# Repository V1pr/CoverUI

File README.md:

# CoverUI for [OpenMower](https://github.com/ClemensElflein/OpenMower)

## About

This repository contains the firmware files required to use the mowers CoverUI (ButtonBoard).

## Variants

1. Custom DIY CoverUI-PCB which replaces the stock (top-cover) PCB.<br>
 Please check the [Cover UI board assembly instructions](<https://openmower.de/docs/cover-ui-assembly/>) for more detailed infos.<br>
 Also available in [Vermut's Shop](https://shop.devops.care/10-openmower) (as part of his 'Upgrade Kit')
1. Stock YardForce CoverUI for the following models:
   1. Classic 500 (STM32 & GD32 MCU)
   2. Classic 500B (STM32 & GD32 MCU)
   3. SA/SC/NX-Type (10 Buttons, 12 LEDs), PCB labeled with RM-ECOW-V1.0.0 (STM32 MCU)
   4. SA/SC/NX-Type (9 Buttons, 11 LEDs), PCB labeled with RM-ECOW-V1.1.0 (STM32 & GD32 MCU)
   5. NX100i (18 Buttons, 3 LEDs, 256*64 Pixel LC-Display), PCB labeled with RM-EC3-V1.1 (STM32 MCU)
   6. SAxPro (Rev6) 6 Buttons 240*128 Pixel LC-Display (STM32 MCU)
   
    For this, you need to solder some cables and flash a modified firmware to it.<br>
    Please check the detailed [Stock CoverUI Readme](Firmware/CoverUI/YardForce/README.md) (as you've also the option to use your stock 'hall', 'stop' and 'rain' cables).

+1. LegacyHAT, a HAT addon for non-uC original CoverUI (9 Buttons, 11 LEDs), HAT uses an STM32F4xx "black pill" (mind the pill size!) - UNTESTED (yet!)

## License

Distributed under the MIT License. See [LICENSE](LICENSE) for more information.

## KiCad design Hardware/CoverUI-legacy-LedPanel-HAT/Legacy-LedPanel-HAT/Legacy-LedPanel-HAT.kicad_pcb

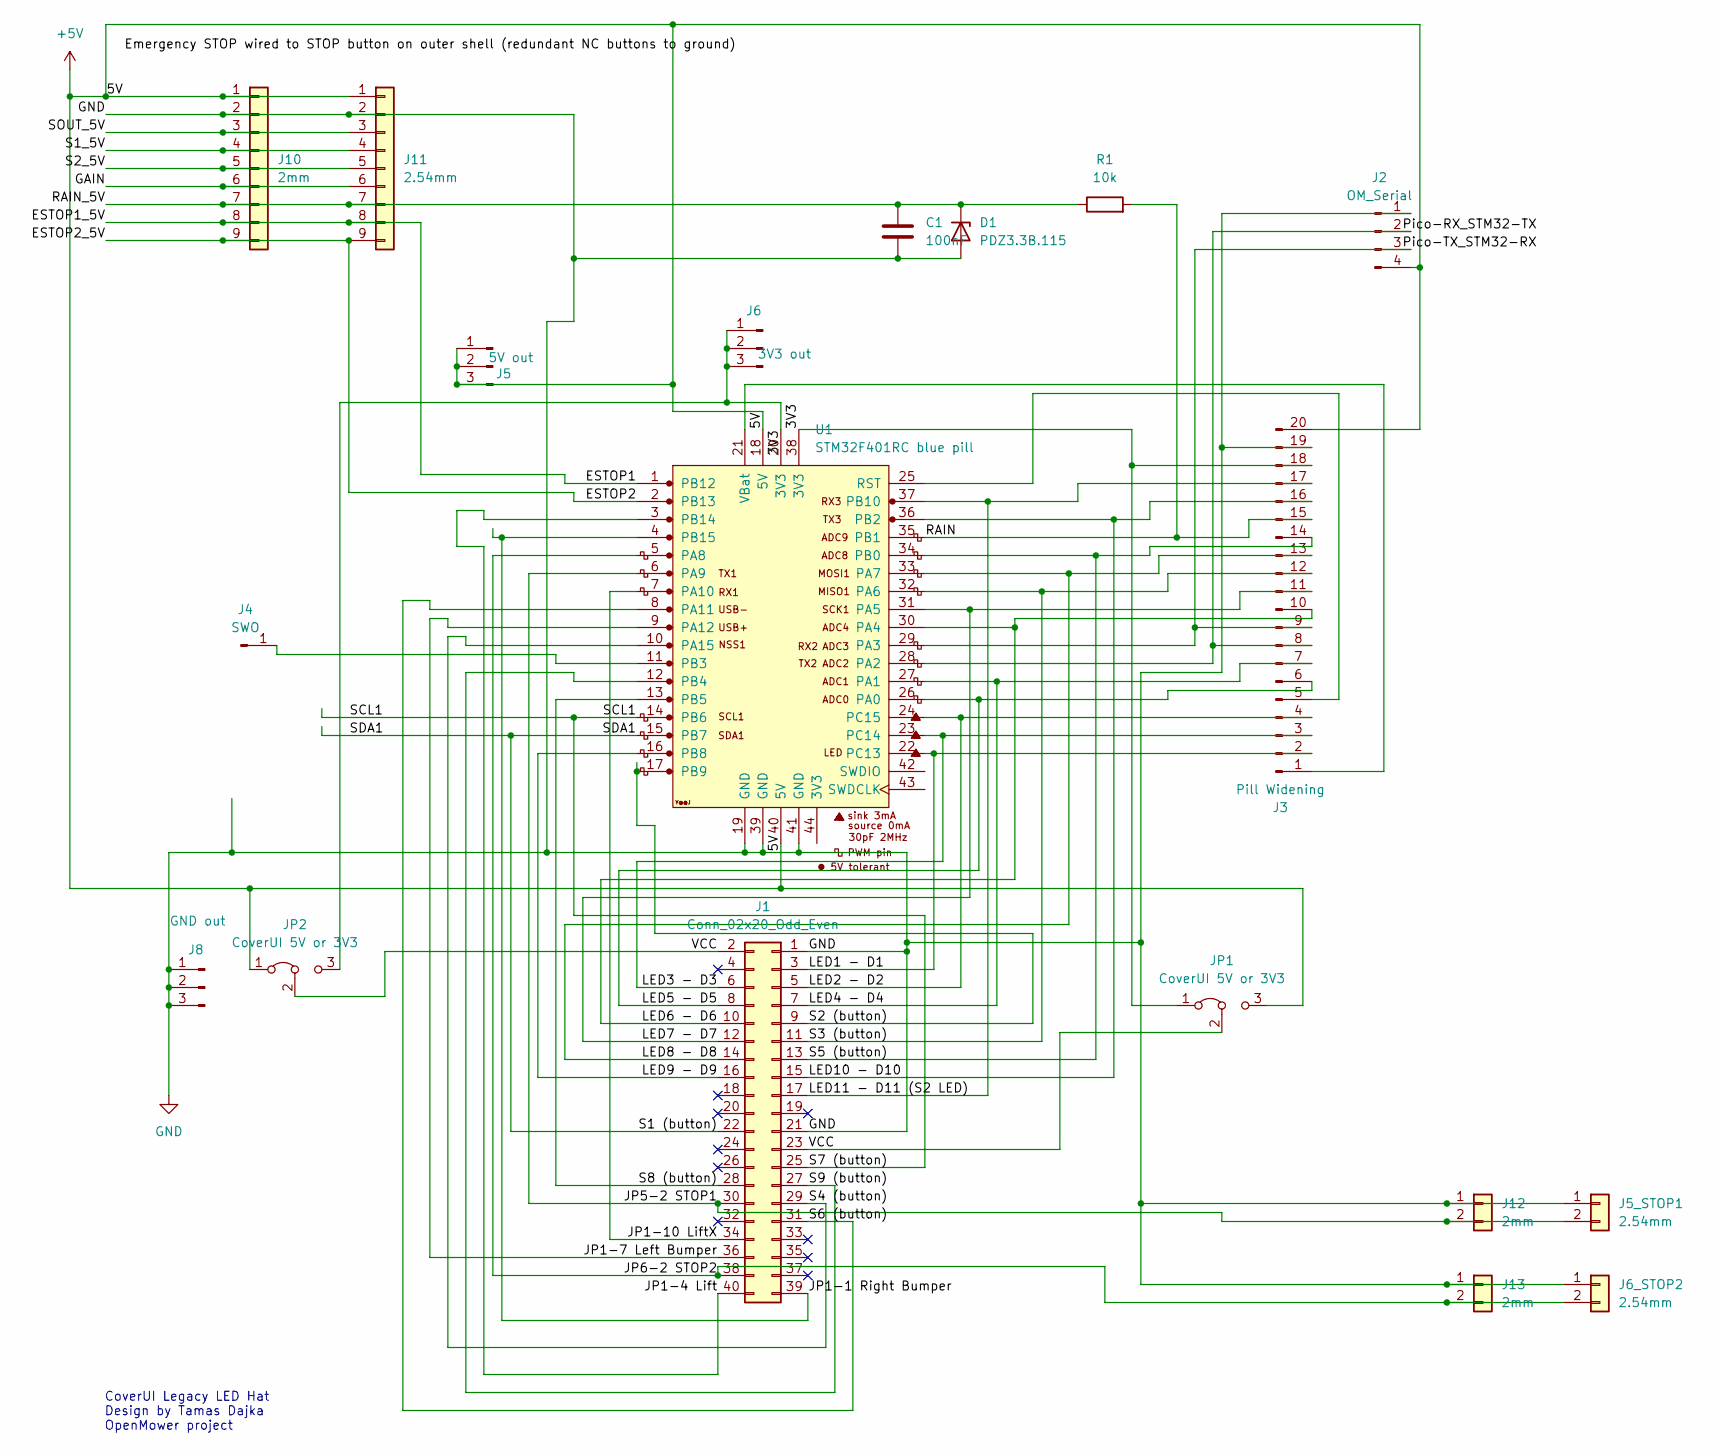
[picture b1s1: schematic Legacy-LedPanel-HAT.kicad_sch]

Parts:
C1: 100nF; C_1812_4532Metric
D1: PDZ3.3B.115; D_1812_4532Metric
J1: Conn_02x20_Odd_Even; PinHeader_2x20_P2.54mm_Vertical
J2: OM_Serial; JST_XH_S4B-XH-A_1x04_P2.50mm_Horizontal
J3: Pill Widening; PinHeader_1x20_P2.54mm_Vertical
J4: SWO; PinHeader_1x01_P2.54mm_Vertical
J5: 5V out; PinHeader_1x03_P2.54mm_Vertical
J5_STOP1, J6_STOP2: 2.54mm; JST_XH_B2B-XH-A_1x02_P2.50mm_Vertical
J6: 3V3 out; PinHeader_1x03_P2.54mm_Vertical
J8: GND out; PinHeader_1x03_P2.54mm_Vertical
J10: 2mm; JST_PH_B9B-PH-K_1x09_P2.00mm_Vertical
J11: 2.54mm; JST_XH_B9B-XH-A_1x09_P2.50mm_Vertical
J12, J13: 2mm; JST_PH_B2B-PH-K_1x02_P2.00mm_Vertical
JP1, JP2: CoverUI 5V or 3V3; PinHeader_1x03_P2.54mm_Vertical
R1: 10k; R_1812_4532Metric_Pad1.30x3.40mm_HandSolder
U1: STM32F401RC blue pill; YAAJ_WeAct_BlackPill_SWD_2

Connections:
+5V: J2.4, J3.20, J5.1, J5.2, J5.3, J10.1, J11.1, JP1.3 (B), JP2.1 (A), U1.18 (5V), U1.40 (5V)
/3V3: J3.18, J6.1, J6.2, J6.3, JP1.1 (A), JP2.3 (B), U1.20 (3V3), U1.38 (3V3)
/ESTOP1: J10.8, J11.8, U1.1 (PB12)
/ESTOP2: J10.9, J11.9, U1.2 (PB13)
/GAIN: J10.6, J11.6
/JP1-1 Right Bumper: J1.39, U1.4 (PB15)
/JP1-4 Lift: J1.40, U1.3 (PB14)
/JP1-7 Left Bumper: J1.36, U1.9 (PA12)
/JP1-10 LiftX: J1.34, U1.7 (PA10)
/JP5-2 STOP1: J1.30, J5_STOP1.2, J12.2, U1.6 (PA9)
/JP6-2 STOP2: J1.38, J6_STOP2.2, J13.2, U1.5 (PA8)
/LED1 - D1: J1.3, J3.2, U1.22 (PC13)
/LED2 - D2: J1.5, J3.4, U1.24 (PC15)
/LED3 - D3: J1.6, J3.3, U1.23 (PC14)
/LED4 - D4: J1.7, J3.7, U1.27 (PA1)
/LED5 - D5: J1.8, J3.6, U1.26 (PA0)
/LED6 - D6: J1.10, J3.10, U1.30 (PA4)
/LED7 - D7: J1.12, J3.11, U1.31 (PA5)
/LED8 - D8: J1.14, J3.13, U1.33 (PA7)
/LED9 - D9: J1.16, U1.16 (PB8)
/LED10 - D10: J1.15, J3.16, U1.36 (PB2)
/LED11 - D11 (S2 LED): J1.17, J3.17, U1.37 (PB10)
/Pico-RX_STM32-TX: J2.2, J3.8, U1.28 (PA2)
/Pico-TX_STM32-RX: J2.3, J3.9, U1.29 (PA3)
/RAIN: J3.15, R1.2, U1.35 (PB1)
/RAIN_5V: C1.1, D1.1 (K), J10.7, J11.7, R1.1
/S1 (button): J1.22, U1.15 (PB7)
/S1_5V: J10.4, J11.4
/S2 (button): J1.9, U1.17 (PB9)
/S2_5V: J10.5, J11.5
/S3 (button): J1.11, J3.12, U1.32 (PA6)
/S4 (button): J1.29, U1.10 (PA15)
/S5 (button): J1.13, J3.14, U1.34 (PB0)
/S6 (button): J1.31, U1.8 (PA11)
/S7 (button): J1.25, U1.14 (PB6)
/S8 (button): J1.28, U1.13 (PB5)
/S9 (button): J1.27, U1.12 (PB4)
/SOUT_5V: J10.3, J11.3
/VCC: J1.2, J1.23, JP1.2 (C), JP2.2 (C)
GND: C1.2, D1.2 (A), J1.1, J1.21, J2.1, J3.19, J5_STOP1.1, J6_STOP2.1, J8.1, J8.2, J8.3, J10.2, J11.2, J12.1, J13.1, U1.19 (GND), U1.39 (GND), U1.41 (GND)
unnamed: J3.1, U1.21 (VBat)
unnamed: J3.5, U1.25 (RST)
unnamed: J4.1, U1.11 (PB3)

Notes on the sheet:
CoverUI Legacy LED Hat Design by Tamas Dajka OpenMower project

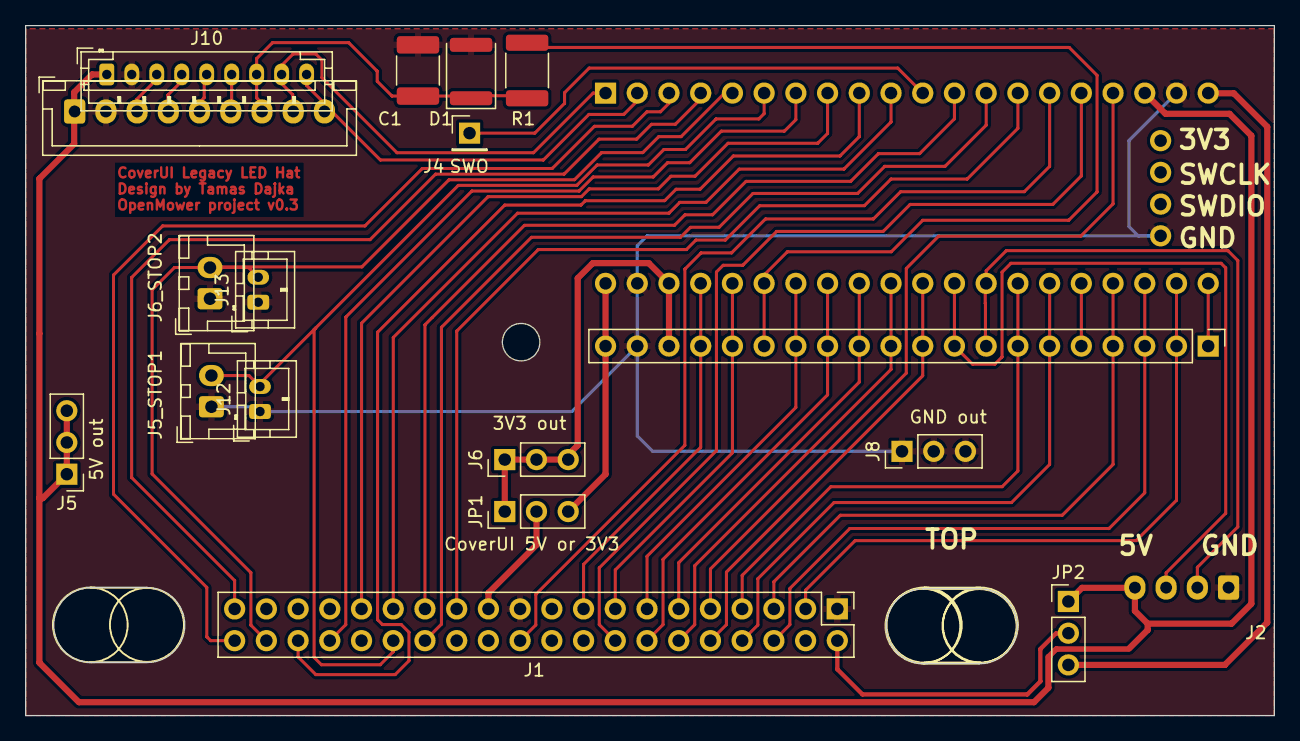
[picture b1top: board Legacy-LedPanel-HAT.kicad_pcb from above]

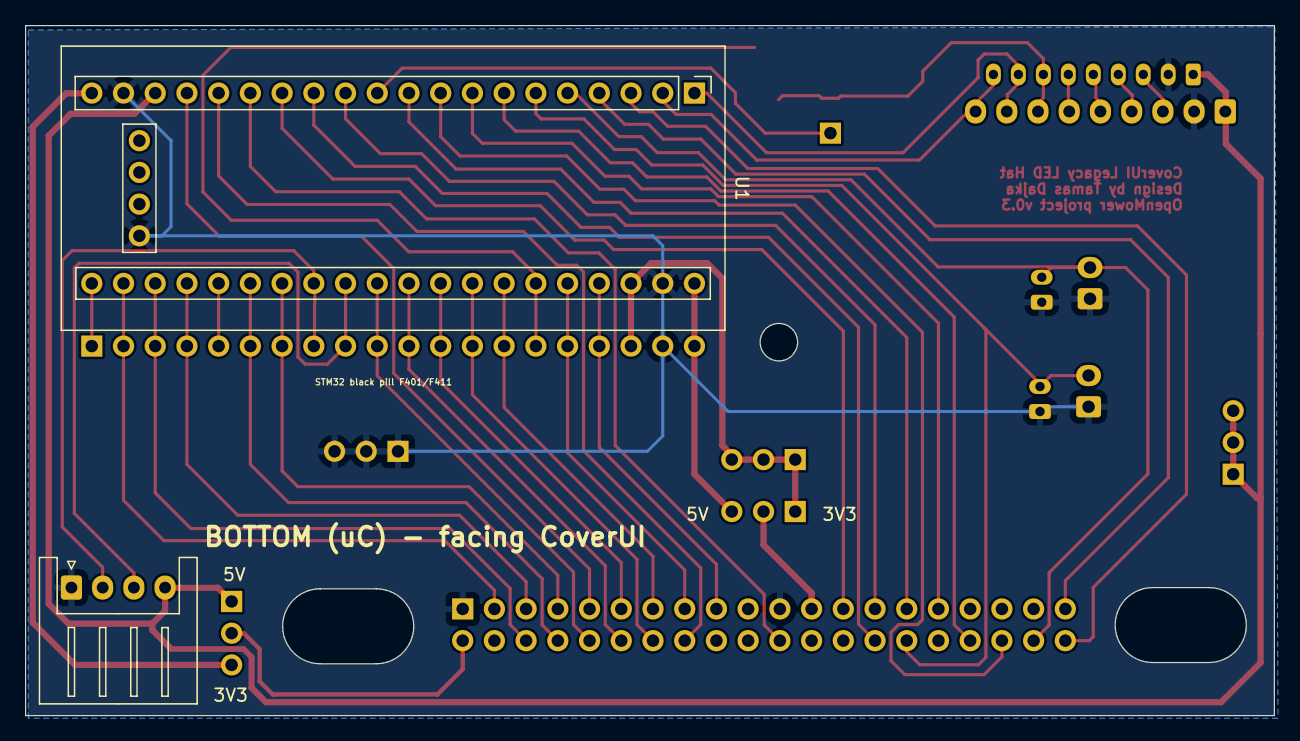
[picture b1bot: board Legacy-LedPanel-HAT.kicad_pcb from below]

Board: 2 copper layers, 100.0 x 55.3 mm, 19 parts (2 on the bottom side), 43 nets.

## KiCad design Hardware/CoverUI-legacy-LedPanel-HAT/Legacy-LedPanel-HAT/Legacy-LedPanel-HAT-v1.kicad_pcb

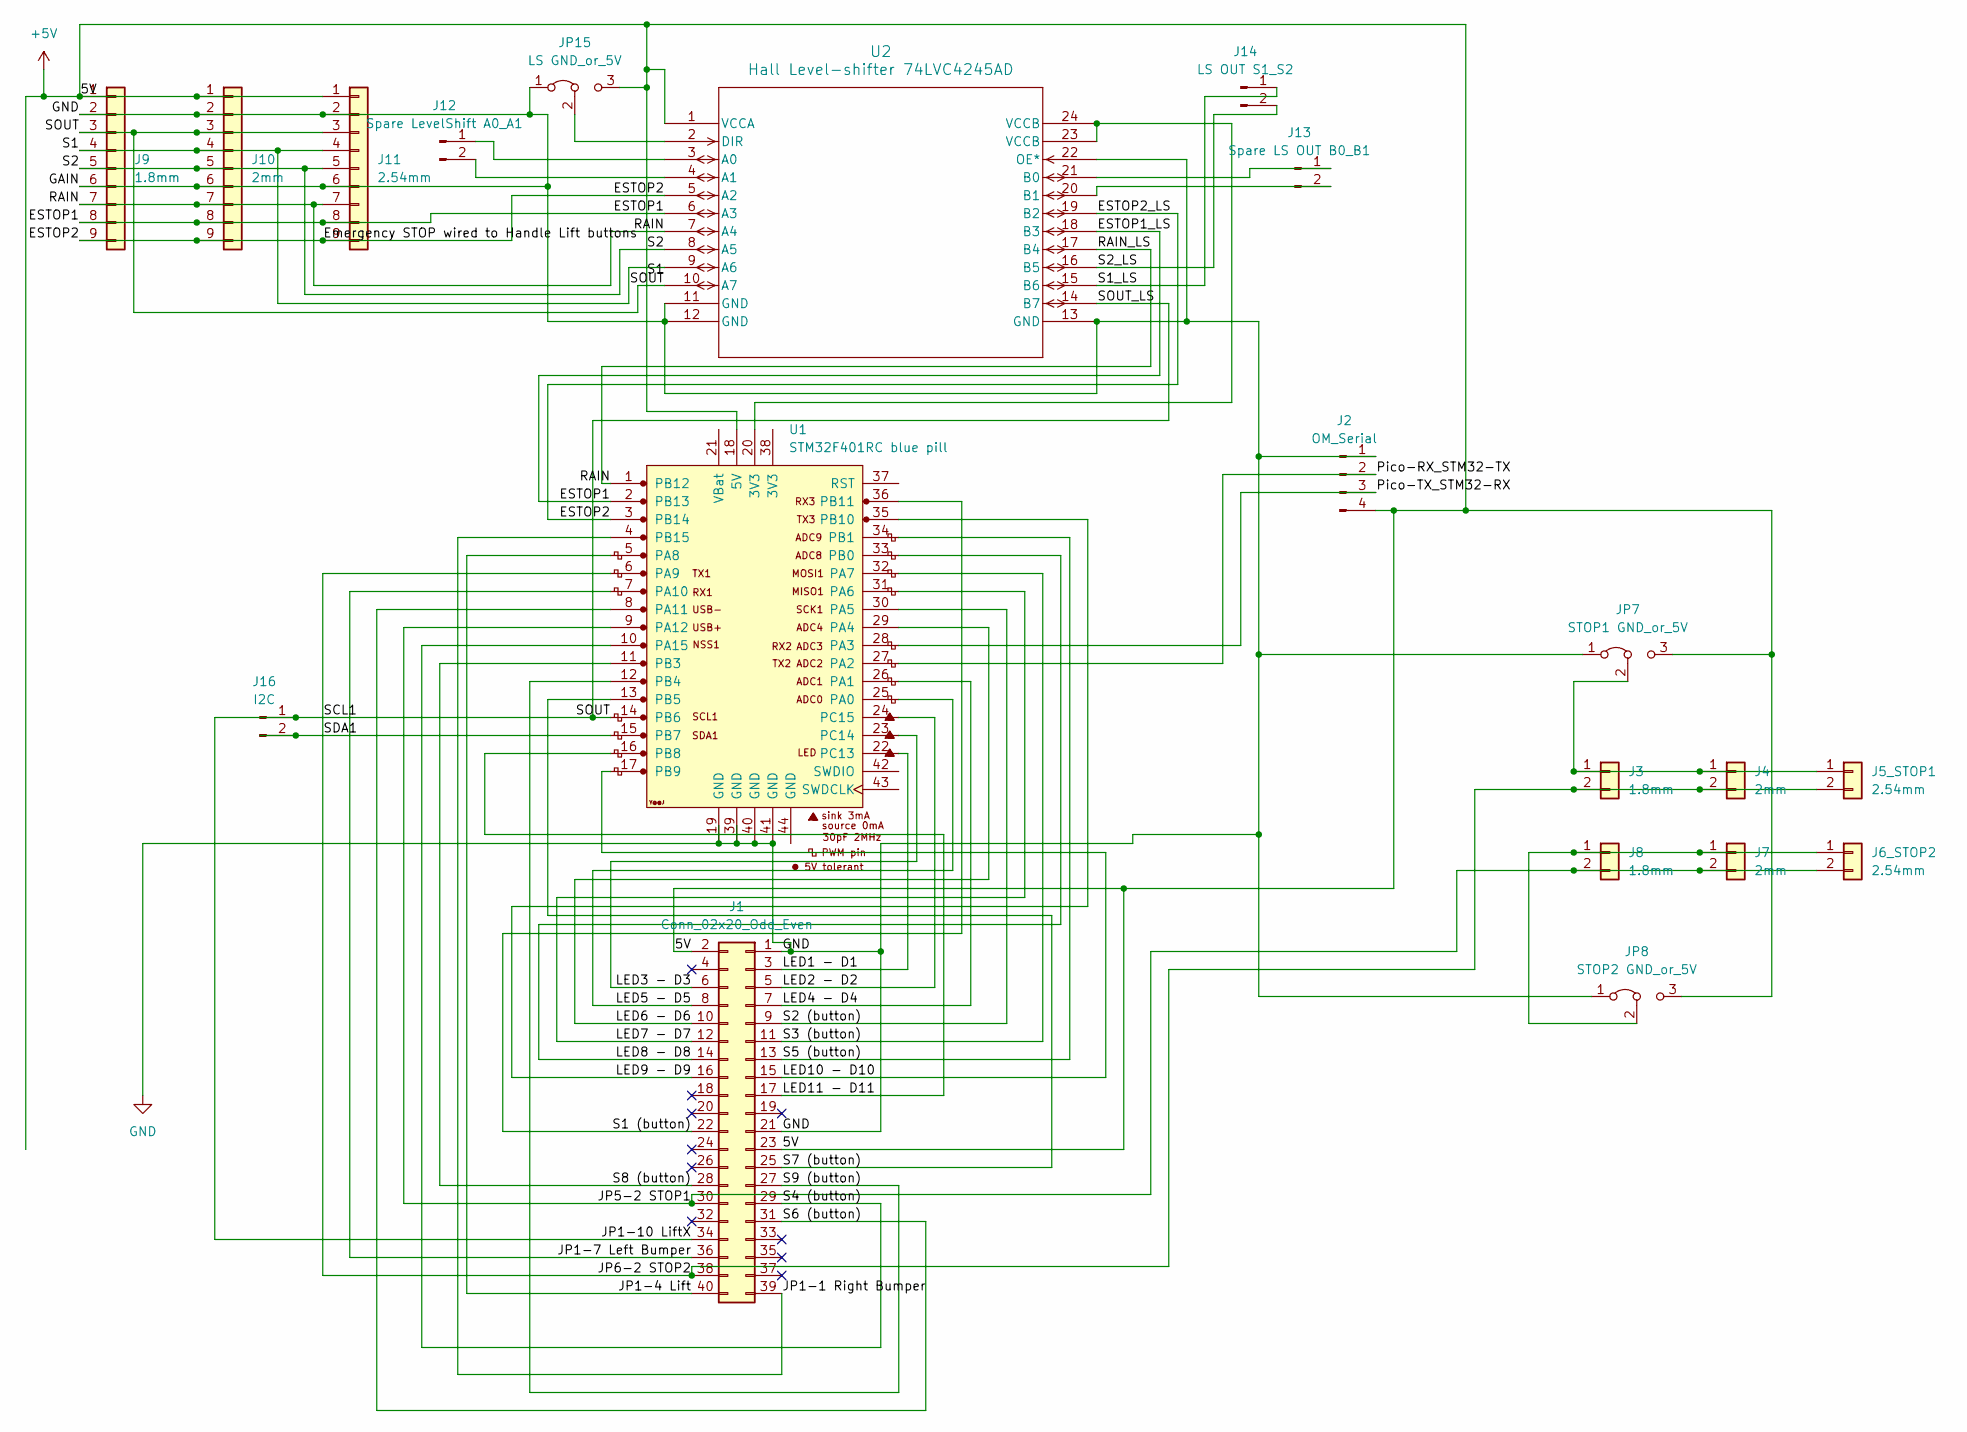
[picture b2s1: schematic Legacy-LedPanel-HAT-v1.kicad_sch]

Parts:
J1: Conn_02x20_Odd_Even; PinHeader_2x20_P2.54mm_Vertical
J2: OM_Serial; JST_XH_S4B-XH-A_1x04_P2.50mm_Horizontal
J3, J8: 1.8mm; conn_01x2_1.8mm
J4, J7: 2mm; JST_PH_B2B-PH-K_1x02_P2.00mm_Vertical
J5_STOP1, J6_STOP2: 2.54mm; JST_XH_B2B-XH-A_1x02_P2.50mm_Vertical
J9: 1.8mm; conn_01x9_1.8mm
J10: 2mm; JST_PH_S9B-PH-K_1x09_P2.00mm_Horizontal
J11: 2.54mm; JST_XH_S9B-XH-A-1_1x09_P2.50mm_Horizontal
J12: Spare LevelShift A0_A1; PinHeader_1x02_P2.54mm_Horizontal
J13: Spare LS OUT B0_B1; PinHeader_1x02_P2.54mm_Horizontal
J14: LS OUT S1_S2; PinHeader_1x02_P2.54mm_Horizontal
J16: I2C; PinHeader_1x02_P2.54mm_Horizontal
JP7: STOP1 GND_or_5V; PinHeader_1x03_P2.54mm_Vertical
JP8: STOP2 GND_or_5V; PinHeader_1x03_P2.54mm_Vertical
JP15: LS GND_or_5V; PinHeader_1x03_P2.54mm_Vertical
U1: STM32F401RC blue pill; YAAJ_BluePill_SWD_1
U2: Hall Level-shifter 74LVC4245AD; SOT137-1_NEX

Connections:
+5V: J1.2, J1.23, J2.4, J9.1, J10.1, J11.1, JP7.3 (B), JP8.3 (B), JP15.3 (B), U1.18 (5V), U2.1 (VCCA)
/ESTOP1: J9.8, J10.8, J11.8, U1.2 (PB13), U2.6 (A3), U2.18 (B3)
/ESTOP2: J9.9, J10.9, J11.9, U1.3 (PB14), U2.5 (A2), U2.19 (B2)
/JP1-1 Right Bumper: J1.39, U1.4 (PB15)
/JP1-4 Lift: J1.40, U1.5 (PA8)
/JP1-7 Left Bumper: J1.36, U1.7 (PA10)
/JP5-2 STOP1: J1.30, J6_STOP2.2, J7.2, J8.2, U1.9 (PA12)
/LED1 - D1: J1.3, U1.22 (PC13)
/LED2 - D2: J1.5, U1.24 (PC15)
/LED3 - D3: J1.6, U1.23 (PC14)
/LED4 - D4: J1.7, U1.26 (PA1)
/LED5 - D5: J1.8, U1.25 (PA0)
/LED6 - D6: J1.10, U1.29 (PA4)
/LED7 - D7: J1.12, U1.31 (PA6)
/LED8 - D8: J1.14, U1.33 (PB0)
/LED9 - D9: J1.16, U1.35 (PB10)
/LED10 - D10: J1.15, U1.17 (PB9)
/LED11 - D11: J1.17, U1.16 (PB8)
/Pico-RX_STM32-TX: J2.2, U1.27 (PA2)
/Pico-TX_STM32-RX: J2.3, U1.28 (PA3)
/RAIN: J9.7, J10.7, J11.7, U1.1 (PB12), U2.7 (A4), U2.17 (B4)
/S1: J9.4, J10.4, J11.4, U2.9 (A6)
/S1 (button): J1.22, U1.36 (PB11)
/S1_LS: J14.1, U2.15 (B6)
/S2: J9.5, J10.5, J11.5, U2.8 (A5)
/S2 (button): J1.9, U1.30 (PA5)
/S2_LS: J14.2, U2.16 (B5)
/S3 (button): J1.11, U1.32 (PA7)
/S4 (button): J1.29, U1.10 (PA15)
/S5 (button): J1.13, U1.34 (PB1)
/S6 (button): J1.31, U1.8 (PA11)
/S7 (button): J1.25, U1.13 (PB5)
/S8 (button): J1.28, U1.11 (PB3)
/S9 (button): J1.27, U1.12 (PB4)
GND: J1.1, J1.21, J2.1, J9.2, J9.6, J10.2, J10.6, J11.2, J11.6, JP7.1 (A), JP8.1 (A), JP15.1 (A), U1.19 (GND), U1.39 (GND), U1.40 (GND), U1.41 (GND), U2.11 (GND), U2.12 (GND), U2.13 (GND), U2.22 (OE*)
unnamed: J3.1, J4.1, J5_STOP1.1, JP7.2 (C)
unnamed: J6_STOP2.1, J7.1, J8.1, JP8.2 (C)
unnamed: J12.1, U2.3 (A0)
unnamed: J12.2, U2.4 (A1)
unnamed: J13.1, U2.21 (B0)
unnamed: J13.2, U2.20 (B1)
unnamed: JP15.2 (C), U2.2 (DIR)
unnamed: U1.20 (3V3), U2.23 (VCCB), U2.24 (VCCB)

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
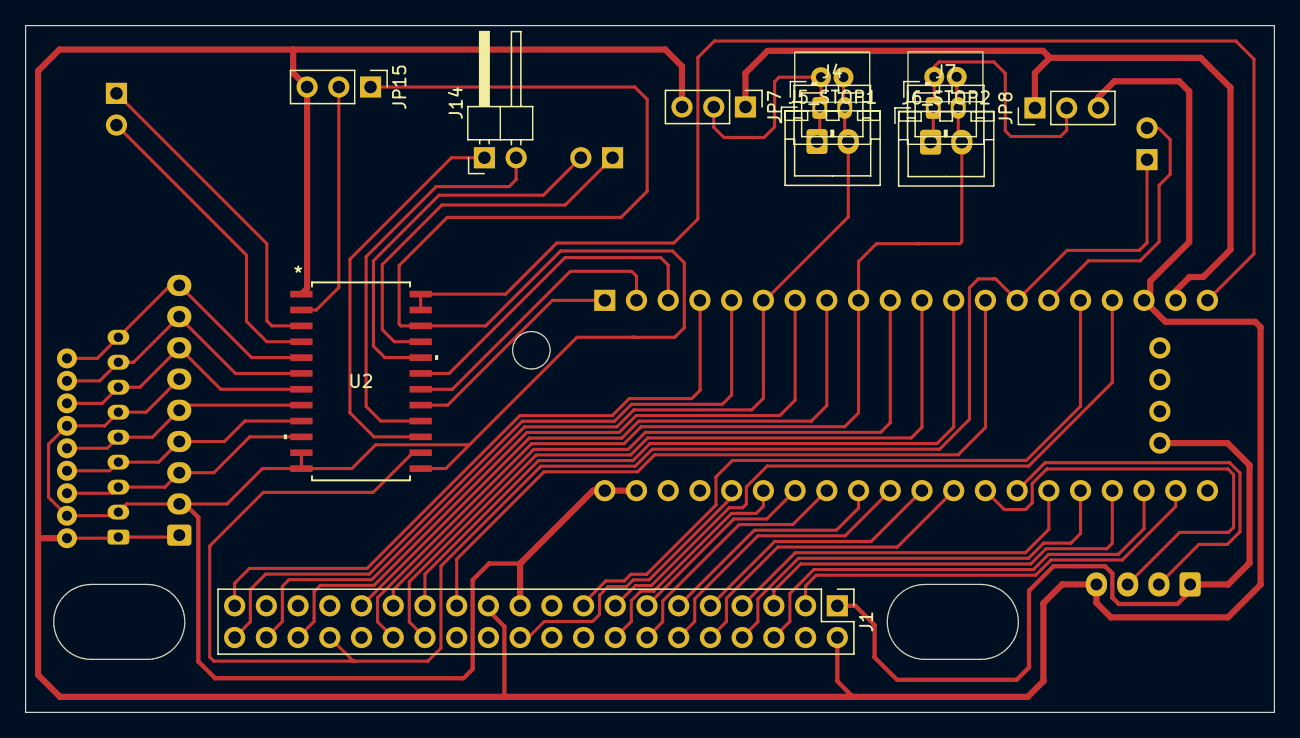
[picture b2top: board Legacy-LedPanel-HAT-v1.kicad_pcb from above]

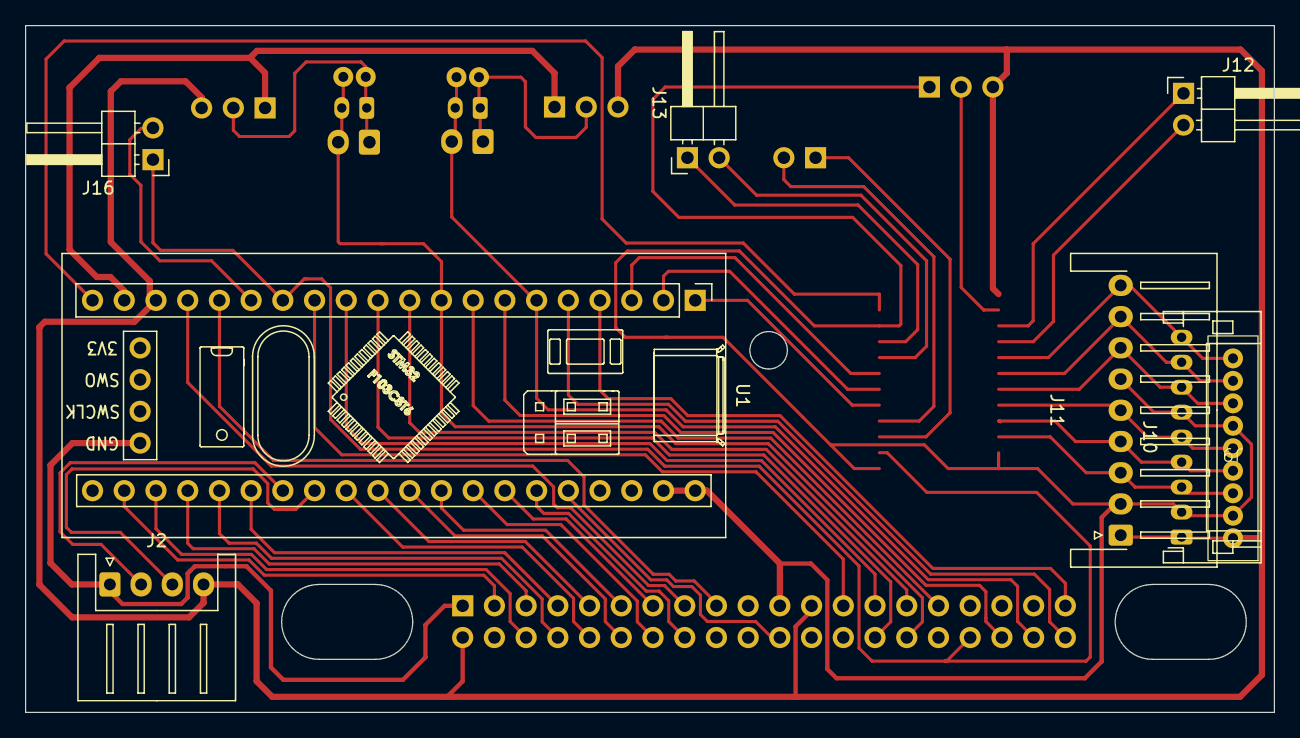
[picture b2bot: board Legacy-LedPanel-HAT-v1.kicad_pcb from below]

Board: 2 copper layers, 100.0 x 55.0 mm, 20 parts (8 on the bottom side), 46 nets.

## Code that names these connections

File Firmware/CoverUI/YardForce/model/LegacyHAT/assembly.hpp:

/**
 * @file model_LEGACYHAT.h
 * @author V1pr <viper @ vipernet (dot) hu>
 * @brief YardForce SA600ECO with non-uC UI panel + HAT module model header for OpenMower https://github.com/ClemensElflein/OpenMower
 * @version 0.1
 * @date 2025-04-15
 *
 * @copyright Copyright (c) 2023, 2024, 2025
 *
 */
#ifndef YARDFORCE_MDL_LEGACYHAT_ASSEMBLY_HPP
#define YARDFORCE_MDL_LEGACYHAT_ASSEMBLY_HPP

#include "../../include/Buttons.hpp"
#include "../../include/main.h"
#include "LEDcontrol.hpp"

#ifdef MOD_EMERGENCY
#include "../../include/Emergency.hpp"
#endif

/*
*
* PA11/PA12 is needed for USB CDC debug to work! Don't use it while debugging!
*
*/

// 1st row: Lifted, Wire (WLAN), Battery empty, Charge
#define LED_PIN_LIFTED PC13
#define LED_PIN_WIRE PC15
#define LED_PIN_BAT PC14
#define LED_PIN_CHARGE PA1

// 2nd row: 4,6,8,10HR
#define LED_PIN_4HR PA4
#define LED_PIN_6HR PA5
#define LED_PIN_8HR PA7
#define LED_PIN_10HR PA0

// 3rd row: S1, S2 + LOCK
#define LED_PIN_S1 PB8
#define LED_PIN_S2 PB10
#define LED_PIN_LOCK PB2 

/*
SW1 - play
SW2 - 10H
SW3 - 4h
SW4 - Home
SW5 - 6H
SW6 - 8H
SW7 - lock
SW8 - S1
SW9 - S2
*/

#define BTN_S1_PIN PB5 // SW8 - D10; PA15
#define BTN_S2_PIN PB4 // SW9 - D11; PB3
#define BTN_PLAY_PIN PB7 // SW1; PB5
#define BTN_HOME_PIN PA15 // SW4;
#define BTN_LOCK_PIN PB6 // SW7 - D9; PB4

#define BTN_4H_PIN PA6 // SW3 - 4H
#define BTN_6H_PIN PB0 // SW5 - 6H
#define BTN_8H_PIN PA11 // SW6 - 8H
#define BTN_10H_PIN PB9 // SW2 - 10H

// STOP button on the outer cover
#define PIN_ESTOP1 PB12 // ESTOP1 from original CoverUI - JP10 on LegacyHAT - 9 pin connector + LevelShift
#define PIN_ESTOP2 PB13 // ESTOP2 from original CoverUI - JP10 on LegacyHAT - 9 pin connector + LevelShift

// handle with 2 switches on either sidesx
#define PIN_HANDLE_BTN_1 PA9 // Handle Button1 - on the LegacyHAT, PB15 if on OEM-CoverUI
#ifndef USBD_USE_CDC // usb CDC debug uses PA11
#define PIN_HANDLE_BTN_2 PA8 // Handle Button2 - on the LegacyHAT, always routed to PA11
#endif

#define PIN_HALL1 PA10 // LiftX - JP1 pin 10 on OEM CoverUI
#ifdef USBD_USE_CDC
#define PIN_HALL2 PB15 // Left bumper - JP1 pin 7 on OEM CoverUI // we fake it to other pin, since PA12 is used by CDC
#else
#define PIN_HALL2 PA12 // Left bumper - JP1 pin 7 on OEM CoverUI
#endif

#define PIN_HALL3 PB14 // Lift - JP1 pin 4 on OEM CoverUI
#define PIN_HALL4 PB15 // Right bumper - JP1 pin 1 on OEM CoverUI

// checkme
#define PIN_RAIN PA1             
#define RAIN_ADC_THRESHOLD 700   // Why a threshold? Cause it could be made configurable on (Stock-)CoverUI (if i.e. required due to inaccuracy)
#define RAIN_PROCESS_PERIOD 5000 // c.ez proposed "once a second or every 10 seconds"

extern LEDcontrolLegacyHAT leds;

class ButtonsLegacyHAT : public Buttons {
    public:
     ButtonsLegacyHAT(const std::map<uint8_t, ButtonDef> &t_kBtnDefByNumMap) : Buttons(t_kBtnDefByNumMap) {};
 
     /**
      * @brief Check if one of the "magic buttons" got pressed and do his function.
      * LOCK + 4H = Display FW version
      * LOCK + 10H = LED animation
      */
     void handle_sys_req() override {
         if (!is_pressed(BTN_LOCK_NUM))
             return;
 
         if (is_pressed(BTN_10H_NUM))
             leds.sequence_start(&LEDcontrol::sequence_animate_handler);
         else if (is_pressed(BTN_4H_NUM))
             leds.show_num(FIRMWARE_VERSION);
         return;
     };
};
 
extern ButtonsLegacyHAT buttons;

// leds and buttons are needed!
#include "Hatch.hpp"

#ifdef MOD_RAIN
#include "../../include/Rain.hpp"
#endif

// LowLevel Serial Pins
#define UART_LL_RX PA3
#define UART_LL_TX PA2

#endif // YARDFORCE_MDL_LEGACYHAT_ASSEMBLY_HPP

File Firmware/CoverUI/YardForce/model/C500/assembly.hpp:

/**
 * @file C500/assembly.hpp
 * @author Apehaenger (joerg@ebeling.ws)
 * @brief YardForce Classic500 CoverUI Assembly for OpenMower https://github.com/ClemensElflein/OpenMower
 * @version 0.1
 * @date 2024-10-02
 *
 * @copyright Copyright (c) 2024
 *
 */
#ifndef YARDFORCE_MDL_C500_ASSEMBLY_HPP
#define YARDFORCE_MDL_C500_ASSEMBLY_HPP

#include "../../include/Buttons.hpp"
#include "../../include/main.h"
#include "LEDcontrol.hpp"

#ifdef MOD_EMERGENCY
#include "../../include/Emergency.hpp"
#endif

// ***** LEDs *****
// 1st row: 2,4,6,8HR
#define LED_PIN_2HR PA4
#define LED_PIN_4HR PA5
#define LED_PIN_6HR PA6
#define LED_PIN_8HR PA7
// 2nd row: S1, S2, LOCK
#define LED_PIN_S1 PA0
#define LED_PIN_S2 PA1
#define LED_PIN_LOCK PC4
// 3rd row: Mon-Sun
#define LED_PIN_MON PA15
#define LED_PIN_TUE PC10
#define LED_PIN_WED PC11
#define LED_PIN_THU PC12
#define LED_PIN_FRI PD2
#define LED_PIN_SAT PB3
#define LED_PIN_SUN PB4
// 4th row: Lifted, Wire, Bat, Charge
#define LED_PIN_LIFTED PC0
#define LED_PIN_WIRE PC1
#define LED_PIN_BAT PC2
#define LED_PIN_CHARGE PC3
// Backside
#define LED_PIN_REAR PB0

// ***** Buttons *****
#define BTN_CLK_PIN PF4
#define BTN_OK_PIN PF5
#define BTN_S1_PIN PB2
#define BTN_S2_PIN PB10
#define BTN_LOCK_PIN PB11
#define BTN_MON_PIN PB12
#define BTN_TUE_PIN PB13
#define BTN_WED_PIN PB14
#define BTN_THU_PIN PB15
#define BTN_FRI_PIN PC6
#define BTN_SAT_PIN PC7
#define BTN_SUN_PIN PC8
#define BTN_PLAY_PIN PA11
#define BTN_HOME_PIN PA12

// ***** Emergency *****
#define PIN_HALL_STOP_WHITE PC5
#define PIN_HALL_STOP_YELLOW PB6
#define PIN_HALL_WHEEL_RED PB7
#define PIN_HALL_WHEEL_BLUE PB8

#define PIN_RAIN PB1             // Need to be soldered with a cable bridge from FB2/JP2 to R79/PB1
#define RAIN_ADC_THRESHOLD 700   // Why a threshold? Cause it could be made configurable on (Stock-)CoverUI (if i.e. required due to inaccuracy)
#define RAIN_PROCESS_PERIOD 5000 // c.ez proposed "once a second or every 10 seconds"


extern LEDcontrolC500 leds;

class ButtonsC500 : public Buttons {
   public:
    ButtonsC500(const std::map<uint8_t, ButtonDef> &t_kBtnDefByNumMap) : Buttons(t_kBtnDefByNumMap) {};

    /**
     * @brief Check if one of the internal button functionality got pressed and do it's function.
     * OK + CLK = Display FW version
     * OK + SUN = LED animation
     */
    void handle_sys_req() override {
        if (!is_pressed(BTN_OK_NUM))
            return;

        if (is_pressed(BTN_SUN_NUM))
            leds.sequence_start(&LEDcontrol::sequence_animate_handler);
        else if (is_pressed(BTN_CLK_NUM))
            leds.show_num(FIRMWARE_VERSION);
        return;
    };
};
extern ButtonsC500 buttons;

#ifdef MOD_RAIN
#include "../../include/Rain.hpp"
#endif

// LowLevel Serial Pins
#define UART_LL_RX PA3
#define UART_LL_TX PA2

#endif  // YARDFORCE_MDL_C500_ASSEMBLY_HPP

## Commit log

2024-08-23 added LegacyHat support for dumb SC600ECO CoverUI; changed Rain support, since SC600ECO also has Rain sensor
2024-08-23 LegacyHAT CoverUI hardware files
2024-08-23 made LegacyHAT more clear
2024-08-24 exclude KiCAD lock file
2025-04-15 commit before merge
2025-04-16 switched LeghacyHAT to new structure
2025-05-23 added USB CDC debug, 401_STOP version works in mower
2025-05-23 HW redesign based on first live tests (new design not tested)
2026-03-14 last version

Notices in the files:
README.md:
License: MIT
